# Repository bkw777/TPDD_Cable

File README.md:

# Cable for [Tandy Portable Disk Drive](http://tandy.wiki/TPDD)

# Parts
PCB & Housing (and solder jig): [PCBWAY](https://www.pcbway.com/project/shareproject/TANDY_Portable_Disk_Drive_Cable.html)  
BOM: [DigiKey](https://www.digikey.com/short/87q1nv0f)  

The BOM includes a grey cable. This [black cable](https://www.digikey.com/short/wbpp81nt) can be substituted if you want.

# Directions

[pictures of build process](build_pics/build_pics.md)
<!--
Assembly pictures: <https://photos.app.goo.gl/TdYxGhzK94KT9rS78>
(old method before the 3d-printed housing)
-->

If you want to make 2 cables, one for Model 100 and one for PC/WP-2, then double the BOM components except for the cable, and cut the cable in half right in the middle.  
Otherwise just cut off the 9-pin plug to make one longer cable for Model 100 and other KC-85 clones.

## prepare the cable

Cut the unwanted plug off the cable.  
If building a Model 100 cable, cut off the 9-pin plug.  
If building a PC/WP-2 cable, cut off the 25-pin plug.  
If building both cables, cut the cable in half in the middle.

Strip off about 1 inch or 25mm of the cable jacket.  
Also cut the foil shield and the bare wire short right at the end of the jacket.

Apply a bit of flux to the ends of the loose wires.

Load up the soldering iron with a ball of solder and touch the soldering iron to the end of each wire long enough for the insulation to shrink itself back about 1-2mm and tin the end of the wire at the same time. You only need about 1mm of wire exposed and it's not worth trying to actually strip the insulation the normal way. Just heat the very tip end and it will melt and shrink itself back the perfect amount and the wire will end up tinned as well.

Insert the cable into the round opening on the housing and push the cable all the way through the housing and slide the housing about a foot back from the end of the cable.

Thread a 1 to 1-1/2 inch (25-30mm) piece of heatshrink onto the cable and slide back to the housing.  
Don't shrink it.

## Map the wire colors to the plug pin numbers

Print the wire color worksheet.

Put a DMM into continuity mode.

Use a jumper wire or meter lead with an alligator clip to grab one of the wires and connect to one lead of the DMM.

Probe with the other meter lead to touch each pin on the DB25 to find which pin that wire goes to.

Write the color of the wire for that pin number on the worksheet.

Repeat for all wires.

Cut the un-used wires short.
For the exact cable in the BOM and probably most cables, there will be 3 wires with no place on the PCB: a bare wire connected to both the DB25 shell and pin 1, a wire on pin 8, and a wire on pin 22.  
Cut all of those as short as possible right at the end of the cable jacket.

## prepare the pcb
Sand the edge of the pcb as neccessary to flatten any pointy bits left from the edge routing. The front edge is supposed to be castellated, so don't try to grind those away, but the front edge is supposed to be straight, so sand flat anything that sticks out from the rest.

Blunt or chamfer the rim of the drill holes on the bottom side of the pcb (the side with the chips). Use a countersink bit if you have one, or a drill bit. If nothing else a phillips screwdriver will barely work. You just want to blunt the sharp edge of the hole so the zip tie can be pulled through, don't grind a deep chamfer.

## solder the pcb
Solder the transistors onto the pcb.

Insert the pcb and the 2x4 connector into the solder jig.  
Face up or down doesn't matter.

Solder the 4 exposed pins on the 2x4 connector.

Remove the pcb from the jig and solder the other 4 pins on the 2x4 connector.

## solder the wires to the pcb
The signal names on the PCB are relative to the computer, aka the DTE side.  
Ex: The pad labelled RTS on the PCB connects to the computers RTS.

Follow your worksheet to match wire colors to the pads on the PCB.

Add solder to the 4 oval wire pads first so that you only need to touch the wire to solder it.

Start with the cable pointing the "wrong" way on the pcb, with the ends of the wires pointing towards the zip tie holes, ie the opposite direction from how it must be in the end, and solder the 4 wires that go to the 4 oval pads.

Then fold the cable over and fish the remaining 3 wires in between the 4 soldered wires towards their respective pins on the 2x4 connector. Keep all 3 of these wires inside of the first 4, ie the 2 outside wires of the 1st 4 remain the outermost wires when done. It's annoying but results in the least pinching & crossing of wires later.

Wash all flux from the pcb and wires.

## assemble the housing
Clean the end of the cable with alcohol where the heat-shrink will go if not done already.

Slide the heat-shrink 2mm past the end of the end of the cable jacket, just enough to cover the unused cut wires and shielding, and shrink it. Don't leave any more heat shrink in front of the jacket than necessary to cover the cut wires. You need to push the cable into the plug body as far as possible later, and excess heat-shrink will prevent the cable from inserting as far as it could.

**Make sure the transistors face DOWN, and the polarity key points UP**.

Slide the housing up over the pcb, or in other words pull the pcb into the housing.

The heat-shrink will want to catch on the front edge of the housing on the way in, and also on an internal lip at the rear of the housing on the way out.  
Squeeze and angle the cable to get the heat-shrink started into front of the housing, and pull the cable on the back 45 degrees up towards the top of the housing before pulling the heat-shrink all the way through so the heat-shrink doesn't catch on a lip at the bottom rear inside the housing.  
Regardless, if the heat-shrink gets dug up on the way through, just heat it again and it will smooth back out.

Once the pcb is all the way in, push the cable forward into the housing as far as possible while holding the pcb in with a finger over the front.  
Make sure the end of the jacket goes past the zip tie area.

Use pliers to put a small extra bend at the very tip of the zip tie, just the last 1-2mm right at the tip, in the same direction it's already bent (the direction it will bend to wrap around the cable).

Insert the zip tie pointing down into the one exposed hole in the pcb you can see, and push in with needle nose pliers until the tip comes out the top. Then you should be able to pull the tie out some more, thread it through the head and pull it the rest of the way. Stop before going all the way tight and jam the cable in as far as possible before cinching down tight.

If you didn't chamfer or blunt the bottom side of the drill holes, then you may have to push the zip tie in with pliers the whole way instead of pulling.

The zip tie does double duty. It both clamps the cable to the pcb and is also what locks the pcb into the housing so the pcb can't pull back out the front.

Once you have tested the cable and are sure the connections are correct, it would be best to inject some glue (C-A/super glue, vynil e6000/goop/etc) into the housing to immobilize the wires and to prevent the cable from working back out of the zip tie. If you're careful you could probably use hot glue by applying some just before inserting the cable, but you'll need to be careful to definitely get some on the pcb all the way back between the holes so that it grabs the heat shrink well, yet not plug up the holes where you will need to push the zip tie through.

## DONE

# Cable Wiring Options

For convenience, the tables below show the wire colors for the specific cables linked here.  
If you buy one of these exact specific cables, then your cable should match one of the tables below, but still double-check the wire colors to pin numbers before soldering.

If you use any other cable that isn't specifically from one of the links here, then ignore the colors in the tables below and map out your cables wire colors yourself with a DMM continuity beeper and one of the printable worksheets below.

The grey cable in the BOM, and the alternative black cable, has both a DB25M on one end and a DE9F on the other end, so you can use the same BOM to make either a "Model T" cable, or a PC cable, or one of each if you double up the other components.

## DB25 Male cable for TRS-80 Model 100 and other KC-85 clones

This is the standard version of the cable that replicates the cable that originally shipped with the TPDD and TPDD2.

The cable in the BOM supports this option.

It supports at least the following machines:

<ul>
Kyotronic KC-85<br>
TRS-80/TANDY Model 100, 102, 200, 600<br>
NEC PC-8201, PC-8300, PC-8401, PC-8500<br>
Olivetti M10

Any other machine with a *female* DB25 DTE RS-232 port. The female part is unusual but some other early machines besides these did have it this way also.
</ul>

[PRINTABLE WIRE COLOR WORKSHEET for KC-85 CLONES](DB25M_DTE_Wire_Chart.pdf)

<table border=1 cellspacing=0>
<caption>TPDD to Model 100</caption>
<tr>
<th colspan=2 width=35%>PCB PAD</th>
<th><a href="https://www.digikey.com/short/w8zz83q5">GREY CABLE</a></th>
<th><a href="https://www.digikey.com/short/wbpp81nt">BLACK CABLE</a></th>
<th colspan=2 width=35%>DB25 PIN</th>
</tr>
<tr>
<td rowspan=99 cellpadding=0></td>
<td>TX</td>
<td>Orange</td>
<td>Red</td>
<td>2</td>
<td rowspan=99 cellpadding=0></td>
</tr>
<!--<tr><td>TX</td><td>Orange</td><td>Red</td><td>2</td></tr>-->
<tr><td>RX</td><td>Red</td><td>Brown</td><td>3</td></tr>
<tr><td>RTS</td><td>Purple</td><td>Blue</td><td>4</td></tr>
<tr><td>CTS</td><td>Grey</td><td>Purple</td><td>5</td></tr>
<tr><td>DSR</td><td>Blue</td><td>Green</td><td>6</td></tr>
<tr><td>GND</td><td>Green</td><td>Yellow</td><td>7</td></tr>
<tr><td>DTR</td><td>Yellow</td><td>Orange</td><td>20</td></tr>
</table>

To verify the final result, check the following with a DMM in Continuity and Diode modes.

<table border=1 cellspacing=0>
<tr>
<th rowspan=99 width=35%></th>
<th>BLACK</th><th>CONT</th><th>DIODE</th><th>RED</th>
<th rowspan=99 width=35%></th>
</tr>
<tr><td>1</td><td>BEEP</td><td></td><td>7</td></tr>
<tr><td>2</td><td>BEEP</td><td></td><td>4</td></tr>
<tr><td>3</td><td></td><td>1.7v</td><td>6</td></tr>
<tr><td>4</td><td></td><td>1.7v</td><td>5</td></tr>
<tr><td>5</td><td>BEEP</td><td></td><td>20</td></tr>
<tr><td>6</td><td></td><td>1.7v</td><td>3</td></tr>
<tr><td>7</td><td>BEEP</td><td></td><td>2</td></tr>
</table>

## DE9 Female cable for Standard PC 9-pin COM port

This version supports:
<ul>
Most PCs with 9-pin com ports<br>
usb-serial adapters<br>
TANDY WP-2<br>
Atari Portfolio<br>
Anything else with a standard male DE9 DTE RS-232 port
</ul>

IE this is for connecting the TPDD directly to a PC, which is not something you usually need to do.

This cable is useful for using [pdd.sh](https://githup.com/bkw777/pdd.sh) to take a raw disk image of a commercial disk or to re-create a disk from a disk image. You don't need this merely to copy normal files, but disks like the utility disks and the sardine dictionary disk are special and can't be copied any other way.

This is also useful if you have a Tandy WP-2 and want to use it's built-in TPDD support.

The cable in the BOM supports this option.

[PRINTABLE WIRE COLOR WORKSHEET for PC/WP-2](DE9F_DTE_Wire_Chart.pdf)

<table border=1 cellspacing=0>
<caption>TPDD to PC</caption>
<tr>
<th colspan=2 width=35%>PCB PAD</th>
<th colspan=2 width=35%>DE9 PIN</th>
</tr>
<tr>
<td rowspan=99 cellpadding=0></td>
<td>RX</td>
<td>2</td>
<td rowspan=99 cellpadding=0></td>
</tr>
<!--<tr><td>RXD</td><td>2</td></tr>-->
<tr><td>TX</td><td>3</td></tr>
<tr><td>DTR</td><td>4</td></tr>
<tr><td>GND</td><td>5</td></tr>
<tr><td>DSR</td><td>6</td></tr>
<tr><td>RTS</td><td>7</td></tr>
<tr><td>CTS</td><td>8</td></tr>
</table>

To verify the final result, check the following with a DMM in Continuity and Diode modes.

<table border=1 cellspacing=0>
<tr>
<th rowspan=99 width=35%></th>
<th>BLACK</th><th>CONT</th><th>DIODE</th><th>RED</th>
<th rowspan=99 width=35%></th>
</tr>
<tr><td>1</td><td>BEEP</td><td></td><td>5</td></tr>
<tr><td>2</td><td>BEEP</td><td></td><td>7</td></tr>
<tr><td>3</td><td></td><td>1.7v</td><td>6</td></tr>
<tr><td>4</td><td></td><td>1.7v</td><td>8</td></tr>
<tr><td>5</td><td>BEEP</td><td></td><td>4</td></tr>
<tr><td>6</td><td></td><td>1.7v</td><td>2</td></tr>
<tr><td>7</td><td>BEEP</td><td></td><td>3</td></tr>
</table>

## Cambridge Z88
**UNTESTED**  
*The Cambridge Z88 RS-232 port has a non-standard pinout.*  
*Do not connect this cable to anything but a Cambridge Z88.*

The cable in the BOM does NOT support this option.  
Delete the cable from the pre-loaded DigiKey cart, and add [this one](https://www.digikey.com/short/mrf9n7nh) instead.

<table border=1 cellspacing=0>
<caption>TPDD to Z88</caption>
<tr>
<th colspan=2 width=35%>PCB PAD</th>
<th colspan=2 width=35%>DE9 PIN</th>
</tr>
<tr>
<td rowspan=99 cellpadding=0></td>
<td>TX</td>
<td>2</td>
<td rowspan=99 cellpadding=0></td>
</tr>
<!--<tr><td>TX</td><td>2</td></tr>-->
<tr><td>RX</td><td>3</td></tr>
<tr><td>RTS</td><td>4</td></tr>
<tr><td>CTS</td><td>5</td></tr>
<tr><td>GND</td><td>7</td></tr>
<tr><td>DSR</td><td>8</td></tr>
<tr><td>DTR</td><td>9</td></tr>
</table>

# Credits / History
In the beginning, there was the [Marty Goodman Document](https://raw.githubusercontent.com/LivingM100SIG/Living_M100SIG/main/M100SIG/Lib-09-PERIFERALS/TPDD.DO), and it was good.

More recently, Rick Shear has taken a new and very careful look at a real cable, and the Marty Goodman doc, and has probably identified the "mystery" components that Marty Goodman talks about. It looks right, and the circuit does indeed work.  
[Rick's initial post](https://rsmicro.wordpress.com/2018/08/26/tpdd-cable/)  
[Rick's follow-up](https://rsmicro.wordpress.com/2018/09/08/built-tpdd-cable-comparison-to-oem/)

This cable uses the same transistors, but a different physical construction.

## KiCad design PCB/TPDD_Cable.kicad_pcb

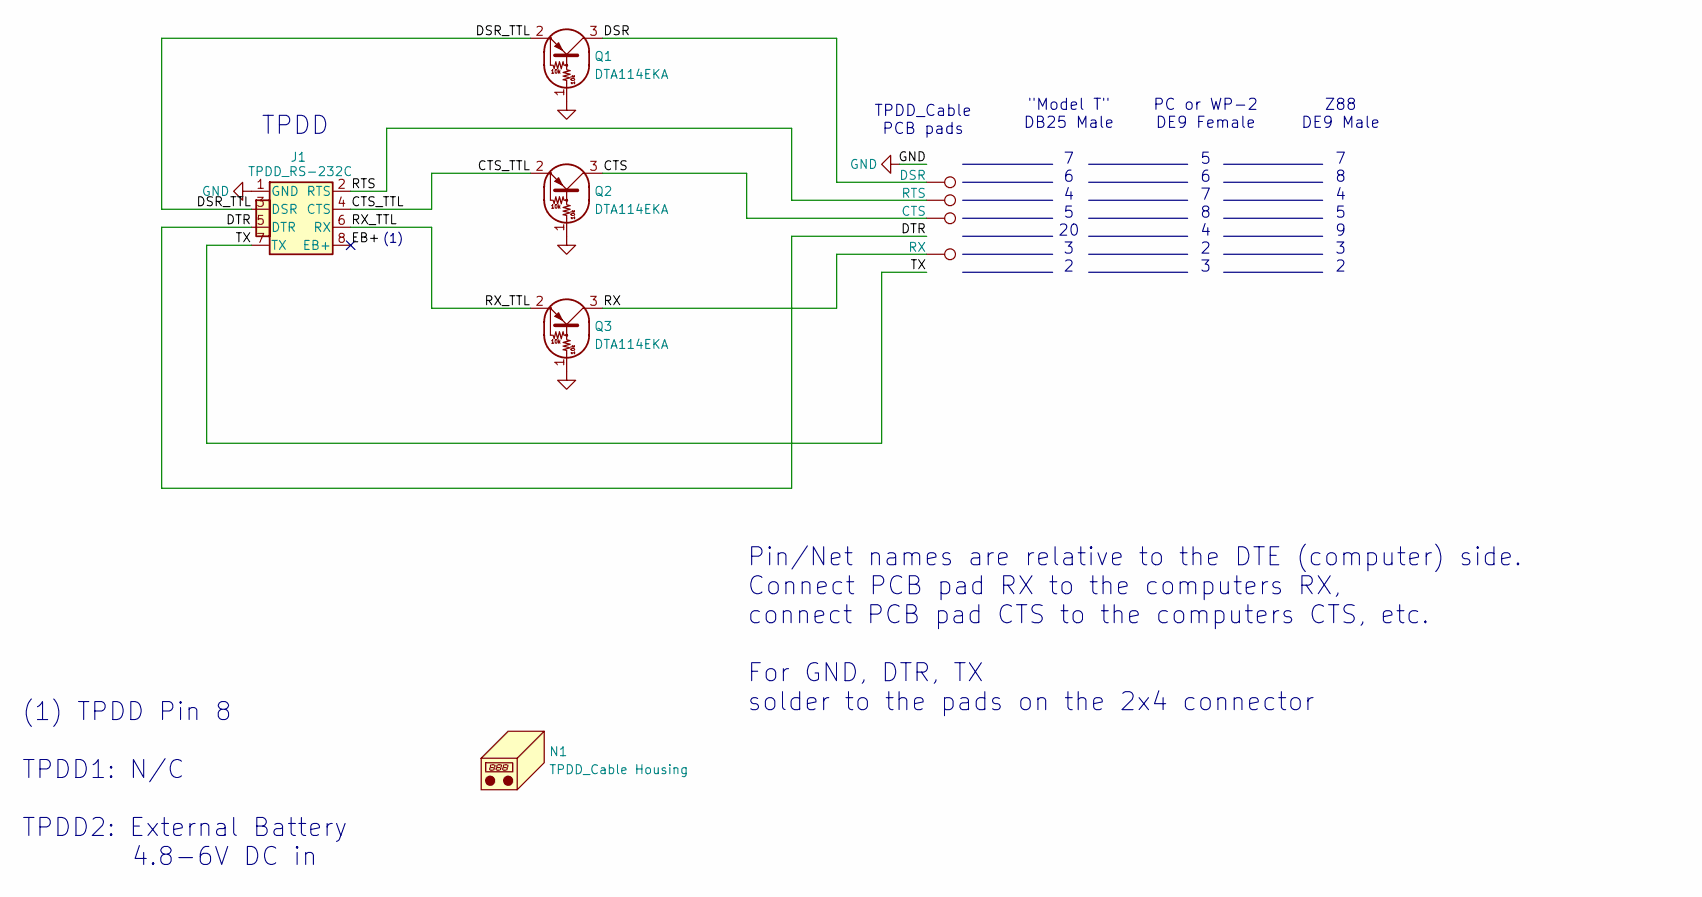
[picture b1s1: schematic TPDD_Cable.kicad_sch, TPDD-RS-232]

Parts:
J1: TPDD_RS-232C; 2x4x2.54mm_edge_mount; MPN M20-7830442
N1: TPDD_Cable Housing; TPDD_Cable_Housing
P3: RX; SMD_1.2x3
P4: RTS; SMD_1.2x3
P5: CTS; SMD_1.2x3
P6: DSR; SMD_1.2x3
Q1, Q2, Q3: DTA114EKA; SC-59; MPN DTA114EKA

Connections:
/CTS: P5.1, Q2.3 (C)
/CTS_TTL: J1.4 (CTS), Q2.2 (E)
/DSR: P6.1, Q1.3 (C)
/DSR_TTL: J1.3 (DSR), Q1.2 (E)
/DTR: J1.5 (DTR)
/EB+: J1.8 (EB+)
/RTS: J1.2 (RTS), P4.1
/RX: P3.1, Q3.3 (C)
/RX_TTL: J1.6 (RX), Q3.2 (E)
/TX: J1.7 (TX)
GND: J1.1 (GND), Q1.1 (B), Q2.1 (B), Q3.1 (B)

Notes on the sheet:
Z88 DE9 Male 7 8 4 5 9 3 2
TPDD_Cable PCB pads
(1) TPDD Pin 8 TPDD1: N/C TPDD2: External Battery 4.8-6V DC in
(1)
Pin/Net names are relative to the DTE (computer) side. Connect PCB pad RX to the computers RX, connect PCB pad CTS to the computers CTS, etc. For GND, DTR, TX solder to the pads on the 2x4 connector
PC or WP-2 DE9 Female 5 6 7 8 4 2 3
TPDD
"Model T" DB25 Male 7 6 4 5 20 3 2

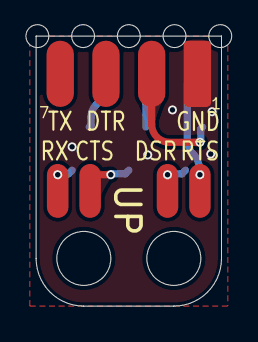
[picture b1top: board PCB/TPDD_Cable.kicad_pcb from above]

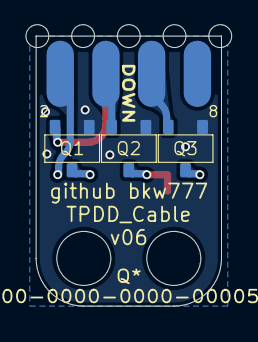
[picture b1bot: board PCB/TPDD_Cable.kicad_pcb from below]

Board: 2 copper layers, 10.3 x 15.0 mm, 9 parts (3 on the bottom side), 8 nets.

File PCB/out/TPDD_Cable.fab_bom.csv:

"Reference","Value","Datasheet","Footprint","Qty","DNP","MPN"
"J1","TPDD_RS-232C","datasheets/M20-783.pdf","000_LOCAL:2x4x2.54mm_edge_mount","1","","M20-7830442"
"Q1,Q2,Q3","DTA114EKA","datasheets/dta114ee3-e.pdf","000_LOCAL:SC-59","3","","DTA114EKA"

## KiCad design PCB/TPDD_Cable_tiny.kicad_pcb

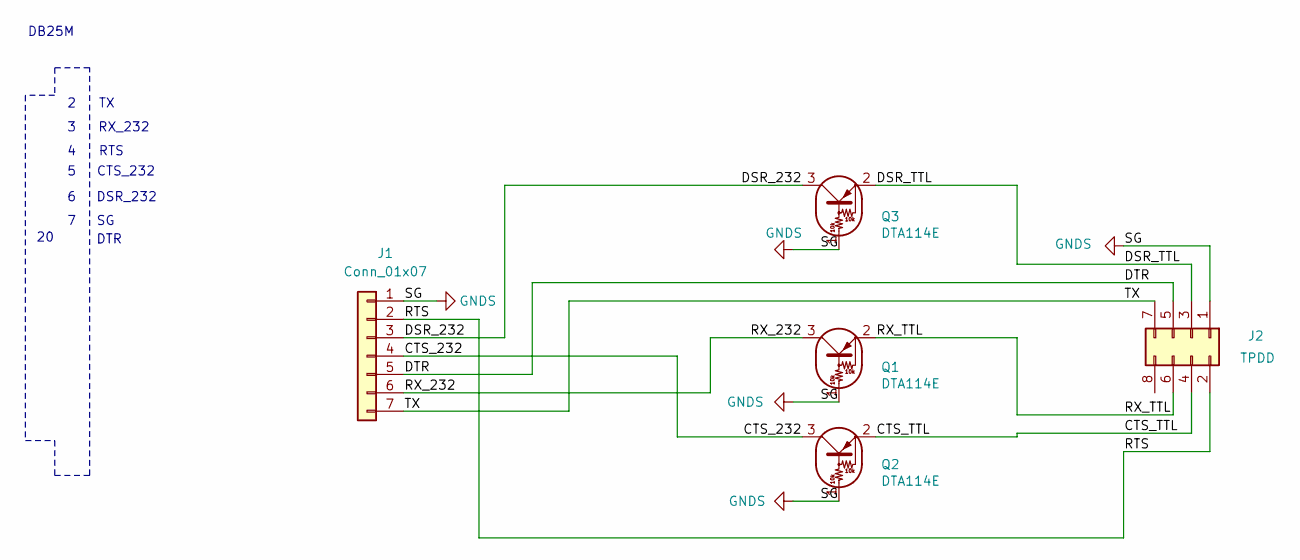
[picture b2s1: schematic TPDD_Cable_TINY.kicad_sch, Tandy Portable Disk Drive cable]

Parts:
J1: Conn_01x07; 1x7x2mm
J2: TPDD; 2x4_header_on_edge
Q1, Q2, Q3: DTA114E; SC-59

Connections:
/CTS_232: J1.4, Q2.3 (C)
/CTS_TTL: J2.4, Q2.2 (E)
/DSR_232: J1.3, Q3.3 (C)
/DSR_TTL: J2.3, Q3.2 (E)
/DTR: J1.5, J2.5
/RTS: J1.2, J2.2
/RX_232: J1.6, Q1.3 (C)
/RX_TTL: J2.6, Q1.2 (E)
/TX: J1.7, J2.7
GNDS: J1.1, J2.1, Q1.1 (B), Q2.1 (B), Q3.1 (B)

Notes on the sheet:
DB25M
RTS
CTS_232
RX_232
DTR
DSR_232

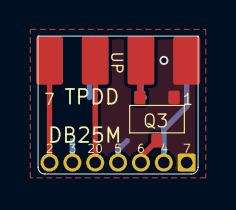
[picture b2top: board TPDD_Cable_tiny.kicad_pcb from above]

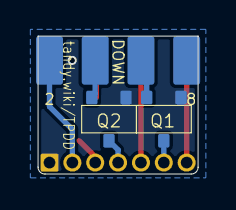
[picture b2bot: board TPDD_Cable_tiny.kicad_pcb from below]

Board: 2 copper layers, 8.9 x 7.7 mm, 5 parts (2 on the bottom side), 10 nets.

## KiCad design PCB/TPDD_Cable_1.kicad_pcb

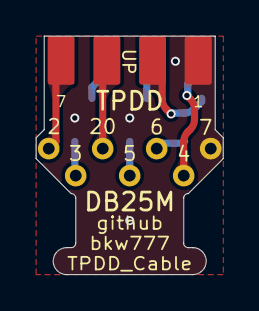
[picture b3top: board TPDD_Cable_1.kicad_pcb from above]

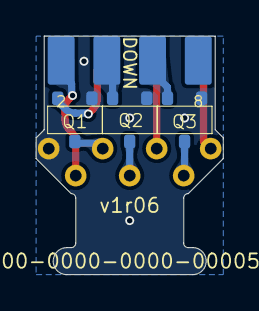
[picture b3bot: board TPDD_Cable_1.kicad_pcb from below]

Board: 2 copper layers, 10.4 x 13.2 mm, 11 parts (3 on the bottom side), 10 nets.

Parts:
J2: TPDD; 2-6-2_tpdd
P2: RX; PTH_0.65x1.2
P3: TX; PTH_0.65x1.2
P4: CTS; PTH_0.65x1.2
P5: RTS; PTH_0.65x1.2
P6: DTR; PTH_0.65x1.2
P7: GND; PTH_0.65x1.2
P20: DSR; PTH_0.65x1.2
Q1, Q2, Q3: DTA114EKA; SC-59

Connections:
/TPDD_Cable/CTS: P5.1, Q2.3 (C)
/TPDD_Cable/CTS_TTL: J2.4, Q2.2 (E)
/TPDD_Cable/DSR: P6.1, Q1.3 (C)
/TPDD_Cable/DSR_TTL: J2.3, Q1.2 (E)
/TPDD_Cable/DTR: J2.5, P20.1
/TPDD_Cable/RTS: J2.2, P4.1
/TPDD_Cable/RX: P3.1, Q3.3 (C)
/TPDD_Cable/RX_TTL: J2.6, Q3.2 (E)
/TPDD_Cable/TX: J2.7, P2.1
GND: J2.1, P7.1, Q1.1 (B), Q2.1 (B), Q3.1 (B)

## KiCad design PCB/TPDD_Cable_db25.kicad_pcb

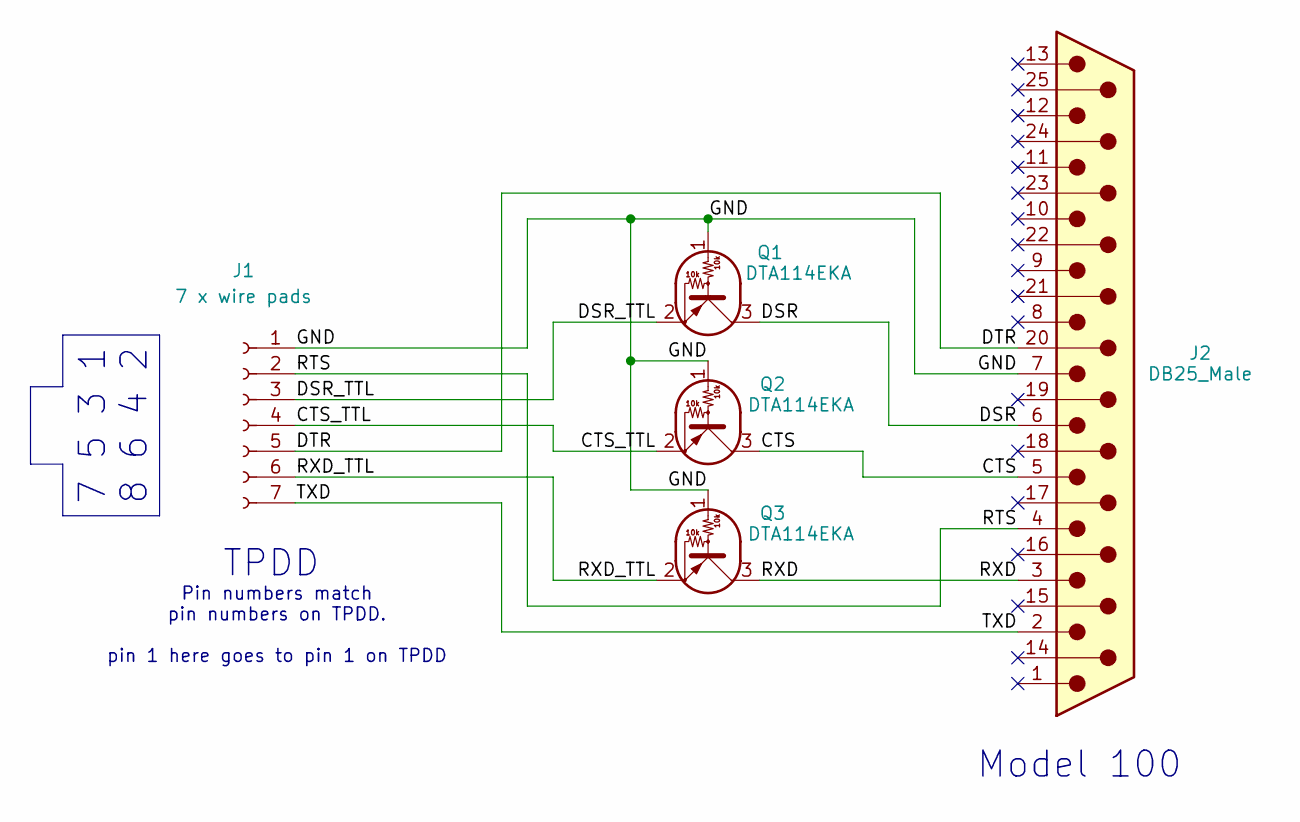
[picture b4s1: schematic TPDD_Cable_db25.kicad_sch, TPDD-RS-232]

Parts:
J1: 7 x wire pads; pins_1x7_2mm
J2: DB25_Male; DSUB-25_Male_EdgeMount_P2.77mm
Q1, Q2, Q3: DTA114EKA; SC-59

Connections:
/CTS: J2.5, Q2.3 (C)
/CTS_TTL: J1.4, Q2.2 (E)
/DSR: J2.6, Q1.3 (C)
/DSR_TTL: J1.3, Q1.2 (E)
/DTR: J1.5, J2.20
/GND: J1.1, J2.7, Q1.1 (B), Q2.1 (B), Q3.1 (B)
/RTS: J1.2, J2.4
/RXD: J2.3, Q3.3 (C)
/RXD_TTL: J1.6, Q3.2 (E)
/TXD: J1.7, J2.2

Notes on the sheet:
7 5 3 1 8 6 4 2
Model 100
TPDD
Pin numbers match pin numbers on TPDD. pin 1 here goes to pin 1 on TPDD

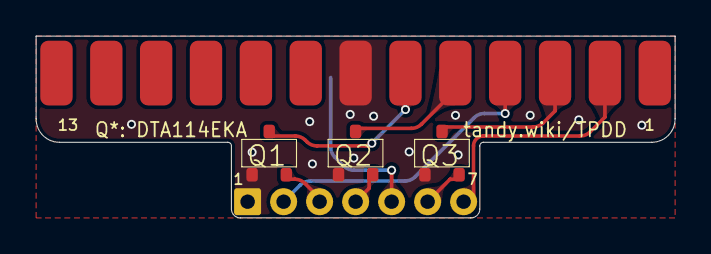
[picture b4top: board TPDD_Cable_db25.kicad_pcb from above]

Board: 2 copper layers, 35.5 x 10.1 mm, 5 parts (0 on the bottom side), 10 nets.

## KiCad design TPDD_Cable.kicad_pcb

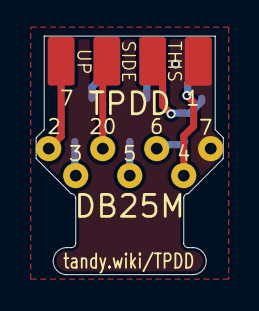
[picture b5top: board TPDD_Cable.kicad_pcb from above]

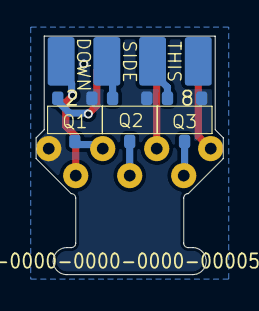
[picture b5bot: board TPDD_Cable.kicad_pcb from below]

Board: 2 copper layers, 10.4 x 13.2 mm, 5 parts (3 on the bottom side), 10 nets.

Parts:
J1: Wire Solder Pads; D7_1.5mm_wirepads
J2: TPDD; 2-6-2_tpdd
Q1, Q2, Q3: DTA114EKA; SC-59

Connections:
/CTS: J1.4, Q2.3
/CTS_TTL: J2.4, Q2.2
/DSR: J1.5, Q1.3
/DSR_TTL: J2.3, Q1.2
/DTR: J1.3, J2.5
/RTS: J1.6, J2.2
/RX: J1.2, Q3.3
/RX_TTL: J2.6, Q3.2
/SG: J1.7, J2.1, Q1.1, Q2.1, Q3.1
/TX: J1.1, J2.7

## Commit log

2020-08-08 initial
2020-08-08 license
2020-08-08 pack v1 board tighter
2020-08-10 cleanup
2020-09-07 remove junk from tracking
2020-09-07 add .gitignore
2020-09-07 add schematic svg for readme
2020-09-07 script to crop svg schematic plots
2020-09-07 add Z88 version
2020-09-23 add WP-2 version, add EB+ in schematics
2020-09-23 temp revert readme to pull
2020-09-23 readme
2021-04-03 pcbway limits, readme
2021-04-26 bigger 2x4 solder pads, smaller wire holes
2021-04-27 adjust board outline
2021-05-25 remove WP-2 and Z88 pcbs, put alternate wiring in readme instead
2021-05-25 pic of Z88 cable pinout
2021-05-25 pcb pad numbers pic
2021-05-25 pic of PC cable pinout
2021-05-25 db25m wiring pic
2021-05-26 action shots
2022-10-02 kicad 6, ground zones
2023-12-20 add cable tests to readme
2023-12-20 better image of tpdd plug end
2024-08-11 3d printed plug housing
2024-08-14 pcb shape v012
2024-08-14 readme & bom
2024-08-15 pcb version 3
2024-08-15 housing & solder jig
2024-08-15 organize files
2024-08-16 plug housing
2024-08-16 silkscreen
2024-08-17 housing 0.8mm min wall
2024-08-18 housing: 0.8mm min-wall & many small fixes. pcb: pull in v1 & v2 pcbs from master & fancy2
2024-08-18 pcb names
2024-08-19 increase housing C max cable diam
2024-08-20 readmes
2024-08-20 housing readme
2024-08-20 pics
2024-10-10 pcb 2 is new default, smt wire pads
2024-10-10 pics filenames
2024-10-12 transistors & wire pads placement
2024-10-23 correct DTE vs DCE signal names & DE9 pinout in schematic
2024-10-23 DTE vs DCE signal names & cable pinouts
2024-10-24 db25 pinout pics, enlarge ziptie holes to 3mm
2024-10-24 schematics notes text
2024-10-24 move via out of smt pad
2024-10-25 build pics
2024-10-25 build_pics.md
2024-10-26 wire color charts
2024-10-30 fab bom & pics
2024-10-31 bom & readme
2024-11-03 update build pics for v06
2024-11-04 schematic less clutter
2024-11-09 wp2 & pc pics
